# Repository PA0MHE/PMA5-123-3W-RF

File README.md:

# RF PCB for 10GHz 3W MMIC PMA5-123-3W+ from Mini Circuits

RF section only requires DC bias board.
Be carefull: 
- Always apply negative Vgg first before applying Vdd
- Ensure very good thermal contact to a heatsink

# PCB

Gerber files are included, Substrate Rogers RO4350 0.51mm

73's Maarten PA0MHE

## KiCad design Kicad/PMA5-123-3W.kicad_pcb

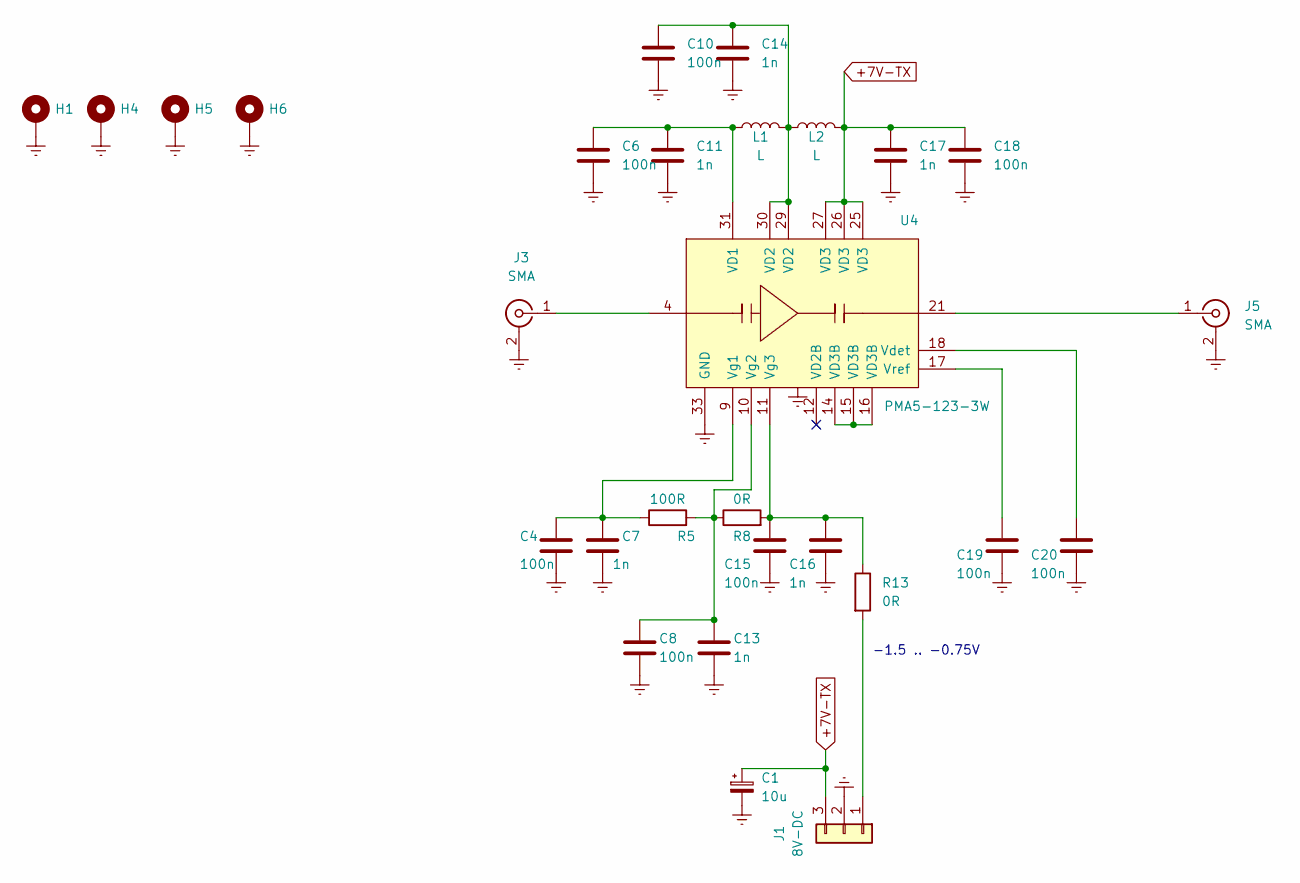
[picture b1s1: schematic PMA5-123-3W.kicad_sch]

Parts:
C1: 10u; C_0805_2012Metric
C4, C6, C8, C10, C15, C18, C19, C20: 100n; C_0603_1608Metric
C7, C11, C13, C14, C16, C17: 1n; C_0603_1608Metric
H1, H4, H5, H6: MountingHole_2.7mm_M2.5_Pad_Via
J1: 8V-DC; KF301-3P
J3, J5: SMA; SMA_clamp
L1, L2: L; L_0603_1608Metric
R5: 100R; R_0603_1608Metric
R8: 0R; R_0603_1608Metric
R13: 0R; R_2010_5025Metric
U4: PMA5-123-3W; QFN-32-1EP_5x5mm_P0.5mm_EP3.1x3.1mm_ThermalVias_PMA5-123

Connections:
+7V-TX: C1.1, C17.1, C18.1, J1.3, L2.2, U4.25 (VD3), U4.26 (VD3), U4.27 (VD3)
GNDREF: C1.2, C4.2, C6.2, C7.2, C8.2, C10.2, C11.2, C13.2, C14.2, C15.2, C16.2, C17.2, C18.2, C19.2, C20.2, H1.1, H4.1, H5.1, H6.1, J1.2, J3.2 (Ext1), J5.2 (Ext1), U4.1, U4.2, U4.3, U4.5, U4.6, U4.7, U4.8, U4.13, U4.19, U4.20, U4.22, U4.23, U4.24, U4.28, U4.32, U4.33 (GND)
unnamed: C4.1, C7.1, R5.1, U4.9 (Vg1)
unnamed: C10.1, C14.1, L1.2, L2.1, U4.29 (VD2), U4.30 (VD2)
unnamed: C6.1, C11.1, L1.1, U4.31 (VD1)
unnamed: C8.1, C13.1, R5.2, R8.1, U4.10 (Vg2)
unnamed: C15.1, C16.1, R8.2, R13.1, U4.11 (Vg3)
unnamed: C19.1, U4.17 (Vref)
unnamed: C20.1, U4.18 (Vdet)
unnamed: J3.1 (In1), U4.4
unnamed: J5.1 (In1), U4.21
unnamed: J1.1, R13.2
unnamed: U4.14 (VD3B), U4.15 (VD3B), U4.16 (VD3B)

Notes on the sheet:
-1.5 .. -0.75V

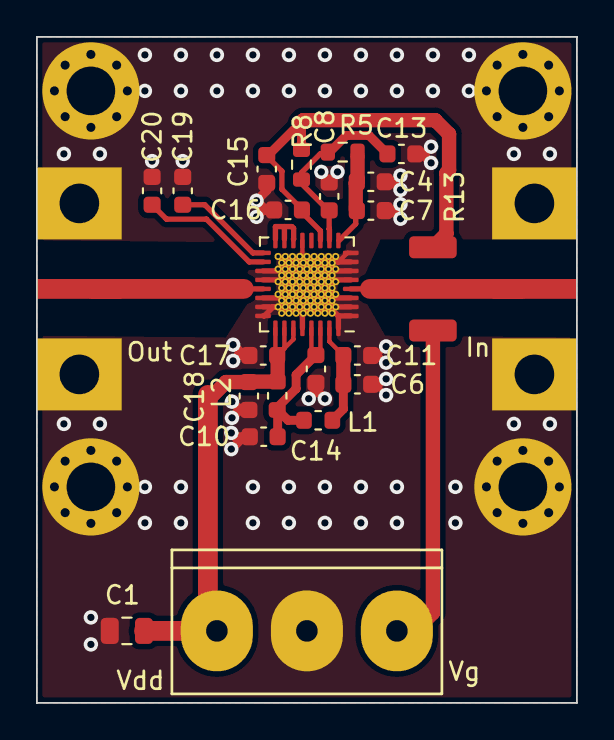
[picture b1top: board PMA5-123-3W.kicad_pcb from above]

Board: 2 copper layers, 30.0 x 37.0 mm, 28 parts (0 on the bottom side), 13 nets.
